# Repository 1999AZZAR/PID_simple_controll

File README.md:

# BLDC Motor PID Controller

High-performance PID control system for maintaining precise RPM control of BLDC motors across multiple microcontroller platforms. Designed for reliability, efficiency, and ease of deployment from prototyping to production.

## Overview

This project provides complete PID controller implementations for BLDC motors, supporting three distinct microcontroller platforms. Each implementation is optimized for specific use cases: from initial development and tuning on Arduino, to cost-effective production deployment on ATtiny85, to advanced embedded applications on ESP32-C3 with wireless connectivity.

### Platform Variants

| Platform | Status | Use Case | Key Features |
|----------|--------|----------|--------------|
| **Arduino Uno** | Development | Prototyping, PID Tuning | Serial debugging, real-time tuning interface |
| **ATtiny85** | Production | Cost-optimized deployment | Minimal footprint, watchdog protection, dual variants |
| **ESP32-C3** | Modern Embedded | High-performance, IoT | FreeRTOS, BLE control, hardware PWM, 200Hz loop |

## Key Features

- **Precise RPM Control**: Advanced PID algorithm with anti-windup and derivative filtering
- **Multiple Filtering Options**: EMA, median, moving average, and sliding window filters
- **Soft-Start Protection**: Configurable ramp-up prevents mechanical stress and current spikes
- **Hardware Optimization**: Platform-specific drivers leverage hardware peripherals for maximum efficiency
- **Safety Features**: Emergency stop, watchdog timers, and input validation
- **Wireless Control**: Optional BLE interface on ESP32-C3 for remote monitoring and control
- **Production Ready**: Proven in real-world applications with comprehensive error handling

## Quick Start

### 1. Choose Your Platform

**For Initial Development**: Start with Arduino Uno to characterize your motor and tune PID constants.

**For Production Deployment**: Use ATtiny85 v1 for direct logic port, or v2 for optimized performance.

**For Advanced Applications**: Choose ESP32-C3 for wireless control, high-speed loops, and RTOS features.

### 2. Hardware Requirements

**Common Components**:
- 3-Phase BLDC Motor with Hall Effect sensors
- Electronic Speed Controller (ESC) with PWM input
- Power supply appropriate for motor voltage requirements
- Microcontroller (Arduino Uno, ATtiny85, or ESP32-C3)

**Platform-Specific**:
- **Arduino Uno**: USB cable for programming, optional potentiometers for tuning
- **ATtiny85**: Arduino Uno as ISP programmer, 10µF capacitor for programming
- **ESP32-C3**: Voltage divider (2.2kΩ/3.3kΩ) if using 5V Hall sensors

### 3. Installation Steps

```bash
git clone https://github.com/your-repo/PID_simple_controll.git
cd PID_simple_controll
```

**Select your platform directory**:
- `arduino_uno/` - Development and tuning platform
- `attiny85/` - Production deployment (v1 or v2)
- `esp32-c3/` - High-performance RTOS platform

**Configure for your motor**:
1. Edit `config.h` to set motor pole count and target RPM
2. Adjust PID gains if you have known values
3. Configure pin assignments if using custom wiring

**Upload firmware**:
- Arduino Uno: Use Arduino IDE directly
- ATtiny85: Program via Arduino as ISP
- ESP32-C3: Use Arduino IDE with ESP32 board support or PlatformIO

## Platform Details

### Arduino Uno (`arduino_uno/`)

**Processor**: ATmega328P @ 16MHz

**Purpose**: Development platform for initial motor characterization and PID tuning.

**Features**:
- Serial Monitor and Plotter output for real-time visualization
- Potentiometer-based live PID tuning (no code recompilation needed)
- Mode switching between normal operation and tuning mode
- Comprehensive debug output
- Emergency stop functionality

**Recommended Workflow**:
1. Connect motor and Hall sensor to Arduino Uno
2. Upload sketch and open Serial Plotter
3. Enable tuning mode and adjust potentiometers
4. Record optimal PID values
5. Transfer values to production platform

### ATtiny85 (`attiny85/`)

**Processor**: ATtiny85 @ 16MHz (PLL mode)

**Purpose**: Cost-effective production deployment with minimal component count.

**Variants**:

**v1 (Recommended)**: Direct logic port from Arduino Uno. If it works on Uno, it works on ATtiny85 v1. Uses floating-point math for identical behavior.

**v2 (Optimized)**: Advanced implementation using hardware timer capture and integer math. More efficient for resource-constrained or high-speed applications.

**Features**:
- Watchdog timer protection prevents system hangs
- Minimal power consumption
- 8-pin DIP package for easy PCB integration
- Emergency stop with automatic recovery
- Proven reliability in production environments

**Pin Configuration**:
- PB3 (Pin 2): Hall sensor input (interrupt capable)
- PB0 (Pin 5): PWM output to ESC
- VCC (Pin 8): 5V power
- GND (Pin 4): Ground

### ESP32-C3 (`esp32-c3/`)

**Processor**: RISC-V @ 160MHz with hardware FPU

**Purpose**: High-performance applications requiring fast control loops, wireless connectivity, or RTOS task management.

**Firmware Variants**:

**Standard (`control/`)**: Always-on motor control with maximum performance.
- 200Hz PID control loop via dedicated FreeRTOS task
- Hardware-accelerated PWM (LEDC peripheral, 5kHz)
- Interrupt-driven RPM sensing with IRAM-resident ISR
- Sliding window filter for stable RPM readings
- Immediate startup on power application

**BLE-Enabled (`control_ble/`)**: Wireless control interface with start/stop commands.
- All features from standard variant
- Bluetooth Low Energy interface (no WiFi interference)
- Real-time status notifications (500ms interval)
- Remote RPM target adjustment
- Thread-safe shared state with spinlock protection
- JSON status format for easy integration

**Motor Simulator (`simulator/`)**: Virtual motor for safe testing and development.
- Simulates motor physics (inertia, acceleration)
- Configurable max RPM and response characteristics
- Optional noise injection for filter testing
- Eliminates need for real motor during algorithm development

**Features**:
- Hardware FPU for fast floating-point calculations
- FreeRTOS ensures deterministic timing
- 3.3V logic level (requires voltage divider for 5V sensors)
- Optional wireless connectivity (BLE)
- Comprehensive debugging via Serial Monitor

## Documentation

### Comprehensive Guides

- **[Hardware Assembly Guide](docs/howto.md)**: Complete wiring guide, pin assignments, and connection diagrams for all platforms
- **[Troubleshooting Guide](docs/mitigation.md)**: Comprehensive diagnosis and solutions for common issues including electrical, mechanical, and software problems
- **[Platform Comparison](docs/COMPARISON.md)**: Detailed technical comparison of features, performance, and use cases

### Platform-Specific Documentation

- **[Arduino Uno](arduino_uno/README.md)**: Development setup and tuning procedures
- **[ATtiny85](attiny85/README.md)**: Production deployment guide and programming instructions
- **[ESP32-C3](esp32-c3/README.md)**: Advanced features, BLE interface, and RTOS architecture

## Configuration

### Motor Configuration

All platforms use a `config.h` file for motor-specific settings:

```cpp
#define PULSES_PER_REV  4     // Set based on motor pole count
#define DEFAULT_TARGET_RPM 1440.0  // Target speed in RPM
```

**Calculating PULSES_PER_REV**: For a motor with N poles using single Hall sensor: `PULSES_PER_REV = N / 2`

Example: 8-pole motor = 4 pulses per revolution

### PID Tuning

PID constants are defined in platform-specific configuration:

```cpp
#define DEFAULT_KP  0.150  // Proportional gain
#define DEFAULT_KI  0.080  // Integral gain
#define DEFAULT_KD  0.015  // Derivative gain
```

**Tuning Process**:
1. Start with Arduino Uno tuning mode using potentiometers
2. Begin with Kp only (set Ki and Kd to 0)
3. Increase Kp until oscillation occurs, then reduce by 30%
4. Add Ki gradually to eliminate steady-state error
5. Add small Kd if overshoot occurs
6. Transfer final values to production platform

## Safety Considerations

1. **Electrical Isolation**: Keep logic power separate from motor power (common ground only)
2. **Voltage Protection**: Use voltage dividers when interfacing 5V sensors with 3.3V logic (ESP32-C3)
3. **Mechanical Safety**: Secure motor firmly and remove propellers during initial testing
4. **Emergency Stop**: Keep power disconnect easily accessible during testing
5. **Current Rating**: Ensure power supply can handle motor startup current (typically 2-3x running current)
6. **Thermal Management**: Monitor ESC and motor temperatures during extended operation

## Troubleshooting Quick Reference

| Issue | Likely Cause | Solution |
|-------|--------------|----------|
| Motor doesn't start | Insufficient PWM threshold | Increase `PWM_MIN_THRESHOLD` to 60-80 |
| RPM reading 2x actual | Wrong `PULSES_PER_REV` | Divide current value by 2 |
| Unstable speed | Poor PID tuning or noise | Reduce Kp by 30%, add filtering |
| Random RPM spikes | Electrical noise | Add 0.1µF capacitor to Hall input |
| ATtiny85 won't program | Missing reset capacitor | Add 10µF between Arduino Reset and GND |
| ESP32-C3 damaged | 5V applied to GPIO | Use voltage divider for all 5V signals |

See [Troubleshooting Guide](docs/mitigation.md) for comprehensive solutions.

## Contributing

Contributions are welcome. Areas of interest:
- Additional microcontroller platform support
- Advanced PID algorithms (adaptive, fuzzy logic)
- Enhanced filtering techniques
- PCB designs for production deployment
- Test cases and validation procedures

Please read [CONTRIBUTING.md](CONTRIBUTING.md) for guidelines.

## License

MIT License - See [LICENSE](LICENSE) file for details.

This project is provided as-is for educational and commercial use. No warranty is provided for fitness for any particular purpose.

## Support

- **Issues**: Report bugs and request features via GitHub Issues
- **Discussions**: Ask questions and share experiences in GitHub Discussions
- **Documentation**: Comprehensive guides available in `docs/` directory

## Acknowledgments

Built with focus on reliability, performance, and practical deployment. Tested in real-world applications across multiple motor types and configurations.

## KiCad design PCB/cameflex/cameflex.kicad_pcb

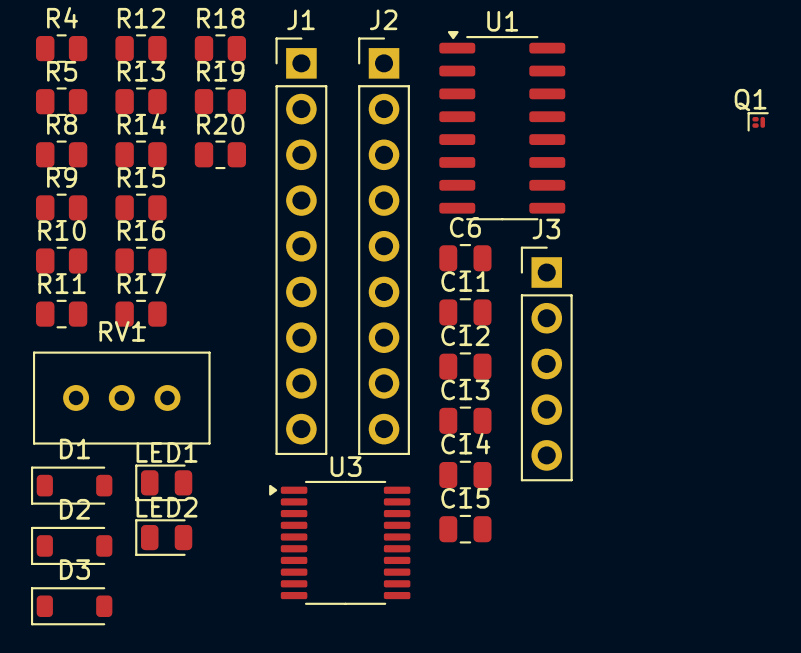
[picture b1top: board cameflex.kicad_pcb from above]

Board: 2 copper layers, 33 parts (0 on the bottom side), 8 nets, no tracks yet.

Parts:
C6, C11: 100nF; C_0805_2012Metric
C12: 470nF; C_0805_2012Metric
C13, C14, C15: 10uF; C_0805_2012Metric
D1, D2, D3: 1N4148; D_SOD-123
J1: ESP32-C3_Left; PinHeader_1x09_P2.54mm_Vertical
J2: ESP32-C3_Right; PinHeader_1x09_P2.54mm_Vertical
J3: CON5_HALL; PinHeader_1x05_P2.54mm_Vertical
LED1: PWR; LED_0805_2012Metric
LED2: ERR; LED_0805_2012Metric
Q1: JY317P; Texas_PicoStar_DFN-3_0.69x0.60mm
R4: 2.2K; R_0805_2012Metric
R5: 3.3K; R_0805_2012Metric
R8, R9, R10, R11, R12, R13: 100R; R_0805_2012Metric
R14, R15, R16, R17, R18, R19: 15R; R_0805_2012Metric
R20: 560R; R_0805_2012Metric
RV1: 10K; Potentiometer_Bourns_3296W_Vertical
U1: JY01(8559); SOP-16_3.9x9.9mm_P1.27mm
U3: JY213L; TSSOP-20_4.4x6.5mm_P0.65mm

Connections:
+3.3V: J1.3, RV1.1
/POT_ADC: J1.6, RV1.2
/RPM_IN: C6.1, J1.4, R4.2, R5.1
GND: C6.2, J1.1, R5.2, RV1.3
unnamed: R10.2, R13.1
unnamed: R14.2, R17.1
unnamed: R15.2, R18.1
unnamed: R16.2, R19.1

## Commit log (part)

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2025-11-06 Initial commit: BLDC Motor PID Controller
    - Arduino Uno implementation with serial tuning capabilities
    - ATTiny85 production implementation optimized for size
    - Complete PID control system with anti-windup protection
    - EEPROM parameter storage and serial command interface
    - Comprehensive documentation and hardware schematics
    - MIT License (c) 2025 azzar budiyanto
2025-11-15 Update documentation and code for BLDC motor controller
    - Changed hardware schematic files from .txt to .md format for better readability.
    - Clarified motor compatibility details in README and code comments, specifying 3-Hall BLDC motors.
    - Enhanced RPM calculation comments to include specific motor examples.
    - Improved consistency in component descriptions across Arduino and ATtiny85 implementations.
    - Removed outdated hardware schematic files to streamline documentation.
2025-11-15 Update README.md to clarify default sensor pulses per revolution for BLDC motors
    - Changed the definition from PULSES_PER_REV to DEFAULT_PULSES_PER_REV for better clarity.
    - Added a note regarding the Arduino Uno version's use of a runtime variable for configurable pulses per revolution.
2025-11-15 Implement advanced safety features and enhance documentation for Arduino Uno and ATtiny85
    - Added watchdog timer functionality to both Arduino Uno and ATtiny85 implementations for improved hang protection.
    - Implemented emergency stop and soft-start protections to enhance motor safety during operation.
    - Updated README.md files for both platforms to include detailed descriptions of new safety features and configuration options.
    - Revised configuration header (config.h) to centralize safety parameters and improve user accessibility.
    - Enhanced overall documentation clarity and organization to better guide users in utilizing the new features.
2025-11-23 Update README.md to include a comprehensive troubleshooting guide and link to mitigation strategies
    - Added a new section in README.md for a mitigation guide to assist users with advanced troubleshooting.
    - Included a link to `mitigation.md`, which covers detailed strategies for addressing common issues such as RPM discrepancies and power supply conflicts.
2025-11-25 Refactor README.md and CI workflows for improved build and packaging process
    - Updated README.md to clarify the automated build and packaging process using GitHub Actions, including detailed sections on output and ZIP contents.
    - Enhanced `compile.yml` to create a complete ZIP package with both source code and compiled firmware, and upload it as an artifact.
    - Revised `create-zip.yml` to focus on generating a source code-only ZIP for manual use, removing dependencies on compiled firmware.
    - Improved documentation structure in workflows to better guide users on triggers and outputs.
2025-11-26 Refactor Arduino Uno PID Controller for simplified operation and enhanced reliability
    - Updated README.md to reflect the streamlined design, removing serial commands and EEPROM storage for a more stable implementation.
    - Revised arduino_uno.ino to eliminate serial tuning and related functions, focusing on potentiometer-based adjustments.
    - Adjusted config.h to remove EEPROM dependencies and simplify configuration.
    - Enhanced documentation to clarify operating modes and tuning procedures, emphasizing the new simplified approach.
2025-12-02 Refine PID controller parameters and documentation for improved performance
    - Updated PID calculations in README.md to include specific values for Kp, Ki, and Kd for gentler control.
    - Adjusted integral windup limits in config.h for more conservative behavior.
    - Changed target RPM reference in arduino_uno.ino to use the defined PRODUCTION_TARGET_RPM for consistency.
    - Enhanced README_flowchart.md to reflect updated anti-windup protection limits.
2025-12-02 Update control loop frequency and RPM calculation intervals for improved performance
    - Changed control loop frequency from 100Hz to 50Hz across multiple files, including README.md, config.h, and howto.md, to enhance system responsiveness.
    - Adjusted RPM calculation interval from 100ms to 50ms for smoother updates.
    - Removed debug information output from the Arduino Uno implementation to streamline operation.
    - Updated flowchart documentation to reflect the new timing specifications.
2025-12-03 Enhance serial communication and PID control in GUI and Arduino code
    - Improved serial port handling in the Python GUI to request exclusive access and flush input/output buffers for better data integrity.
    - Enhanced data processing in the GUI to filter and emit only relevant status messages, reducing noise from corrupted data.
    - Updated Arduino code to remove EEPROM storage, ensuring all parameters are controlled by the Python GUI, and added better handling for low-speed control.
    - Optimized PID output mapping and introduced debug output for troubleshooting during operation.
    - Adjusted control loop timing and improved performance metrics for PID tuning, including enhanced validation and refi
2025-12-03 Enhance PID controller features and update documentation for PPR testing
    - Improved status message handling in the Python GUI to emit additional important messages, including "Ki set" and "Kd set" notifications.
    - Added a new "Test PPR" button in the PIDControllerGUI to verify pulse counting accuracy, allowing users to compare calculated RPM with known motor speeds.
    - Updated README.md to include instructions for the new PPR testing feature, enhancing user guidance on configuring and verifying motor parameters.
    - Adjusted Arduino code to support pulse counting during the PPR test, providing real-time feedback on pulse counts and calculated RPM.
    - Reduced the maximum data points displayed in
2025-12-03 Update howto.md and mitigation.md for improved clarity and consistency
    - Replaced hardcoded RPM values with DEFAULT_TARGET_RPM in howto.md to enhance configurability and maintainability.
    - Updated ESC calibration instructions to use DEFAULT_TARGET_RPM and default PID parameters in howto.md for consistency.
    - Revised RPM reading error description in mitigation.md to reflect the use of DEFAULT_TARGET_RPM for better user understanding.
    - Adjusted PID gain recommendations in mitigation.md to utilize DEFAULT_KP, DEFAULT_KI, and DEFAULT_KD for clarity in tuning guidance.
    - Removed the control_backup.py file as it is no longer needed, streamlining the project structure.
2025-12-04 Refine RPM calculation and filter settings for enhanced performance
    - Further optimized the moving average filter for RPM smoothing, improving accuracy across Arduino and ATtiny85 platforms.
    - Enhanced RPM calculation by refining microsecond timing and adjusting calculation intervals for better responsiveness.
    - Updated configuration parameters to ensure optimal control loop frequency, contributing to overall system performance.
2025-12-05 Enhance RPM control and emergency handling for improved safety and performance
    - Introduced emergency stop logic for extreme RPM errors, ensuring motor safety during unexpected conditions.
    - Updated PWM output handling to allow for direct testing and debugging, facilitating better control authority.
    - Adjusted moving average filter size for RPM calculations to enhance stability across platforms.
    - Refined default PID parameters for improved responsiveness and control stability.
2025-12-06 Remove HTML files from .gitignore to streamline ignored file list
2025-12-13 Update .gitignore and enhance PID controller functionality
    - Added *.db to .gitignore to prevent database files from being tracked.
    - Increased the maximum value for the Ki parameter in the PID controller from 0.2 to 1.0 for improved tuning flexibility.
    - Enhanced plot setup in the PlotCanvas class to include specific line objects for better data visualization.
    - Refactored the refresh_plot method for more efficient data updates and rendering in the UI.
2026-01-10 Update PID parameters, enhance PWM control, and improve flashing script for ATtiny85
    - Adjusted PID output range for better resolution and stability in motor control.
    - Implemented minimum PWM threshold to ensure consistent torque delivery.
    - Updated flashing script to support USB to TTL serial programming, including bootloader installation instructions.
    - Enhanced error handling and user feedback in the flashing process for improved usability.
    - Added detailed documentation for USB to TTL programming and bootloader setup in the FLASHING_GUIDE.md.
2026-01-22 Enhance ATtiny85 PID control with improved features and efficiency
    - Implemented enhanced PID controller with spike dampening, setpoint ramping, and safe emergency handling.
    - Updated PID computation to include derivative-on-measurement and output slew rate limiting for better stability.
    - Optimized memory usage with integer math, achieving 31% flash and 13% RAM utilization.
    - Revised documentation to reflect new features, configuration options, and tuning guidelines for optimal performance.
2026-02-19 Remove deprecated web app files including HTML, CSS, and JavaScript for a cleaner project structure. This cleanup enhances maintainability and focuses the project on core functionalities.
2026-02-19 Remove bootloader script and documentation for ATtiny85 to streamline project structure and eliminate deprecated files.
2026-02-20 Remove ATtiny85 project files to streamline repository
    - Deleted main firmware file (attiny85.ino) and associated configuration headers for improved clarity and maintainability.
    - Removed compilation and flashing scripts, along with documentation, to eliminate deprecated assets and focus on core functionalities.
    - This cleanup enhances the overall project structure and reduces complexity.
2026-02-20 Enhance compile workflow for multiple platforms
    - Added installation steps for the ESP32 core to the GitHub Actions workflow.
    - Updated compilation steps for ATtiny85 sketches, differentiating between v1 (Production Logic Port) and v2 (Advanced Timer).
    - Introduced compilation for ESP32-C3 Control, ensuring proper directory structure and output management.
    - Improved output listing and memory usage checks for all platforms, enhancing clarity in the compiled files and results.
2026-02-20 Update ATTinyCore installation step in GitHub Actions workflow
    - Changed the installation command for ATTinyCore to use 'config add' instead of 'config init' to prevent overwriting existing configurations and avoid path issues.
    - Improved comments for better clarity regarding the configuration process.
2026-02-20 Update Arduino CLI workflow to switch to Damellis ATTiny core
    - Replaced the board manager URL for ATTinyCore with Damellis' core due to reliability issues with Spence Konde's servers.
    - Removed manual download steps for the ATTinyCore index, simplifying the workflow.
    - Updated compilation commands to reflect the new core and ensure correct options for ATtiny85 sketches.
    - Enhanced comments for clarity on the changes made to the installation and compilation processes.
2026-03-01 Refactor RPM filtering and control logic for ESP32-C3
    - Removed the exponential moving average (EMA) implementation and replaced it with a sliding window filter for RPM calculations, improving accuracy and responsiveness.
    - Updated global variables related to RPM control to be volatile for better thread safety.
    - Simplified the soft start logic in the PWM application to enhance readability and maintainability.
